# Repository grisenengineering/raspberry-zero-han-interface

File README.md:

# raspberry-zero-han-interface

## Intruduction
This is a simple PCB to allow a raspberry pi zero to connect to smart meters to gather statistics of power comsumption and similar. 
It uses the HAN-interface that many new meters have and converts it to UART signals to the raspberry pi zero.

It adds as a shield for the raspbery pi zero and provides power to the pi from the 5V-line in the HAN-interface. 
The HAN-interface is specified for 250mA max, so even though is could be plugged in to a normal a normal raspberry pi, it is not a good idea...

This board uses a RJ12-connector. Swedish smart meters use this connector and many other countries at least in the EU, but there are variations.

THE BOARD IS NOT TESTED, USE AT YOUR OWN RISK!

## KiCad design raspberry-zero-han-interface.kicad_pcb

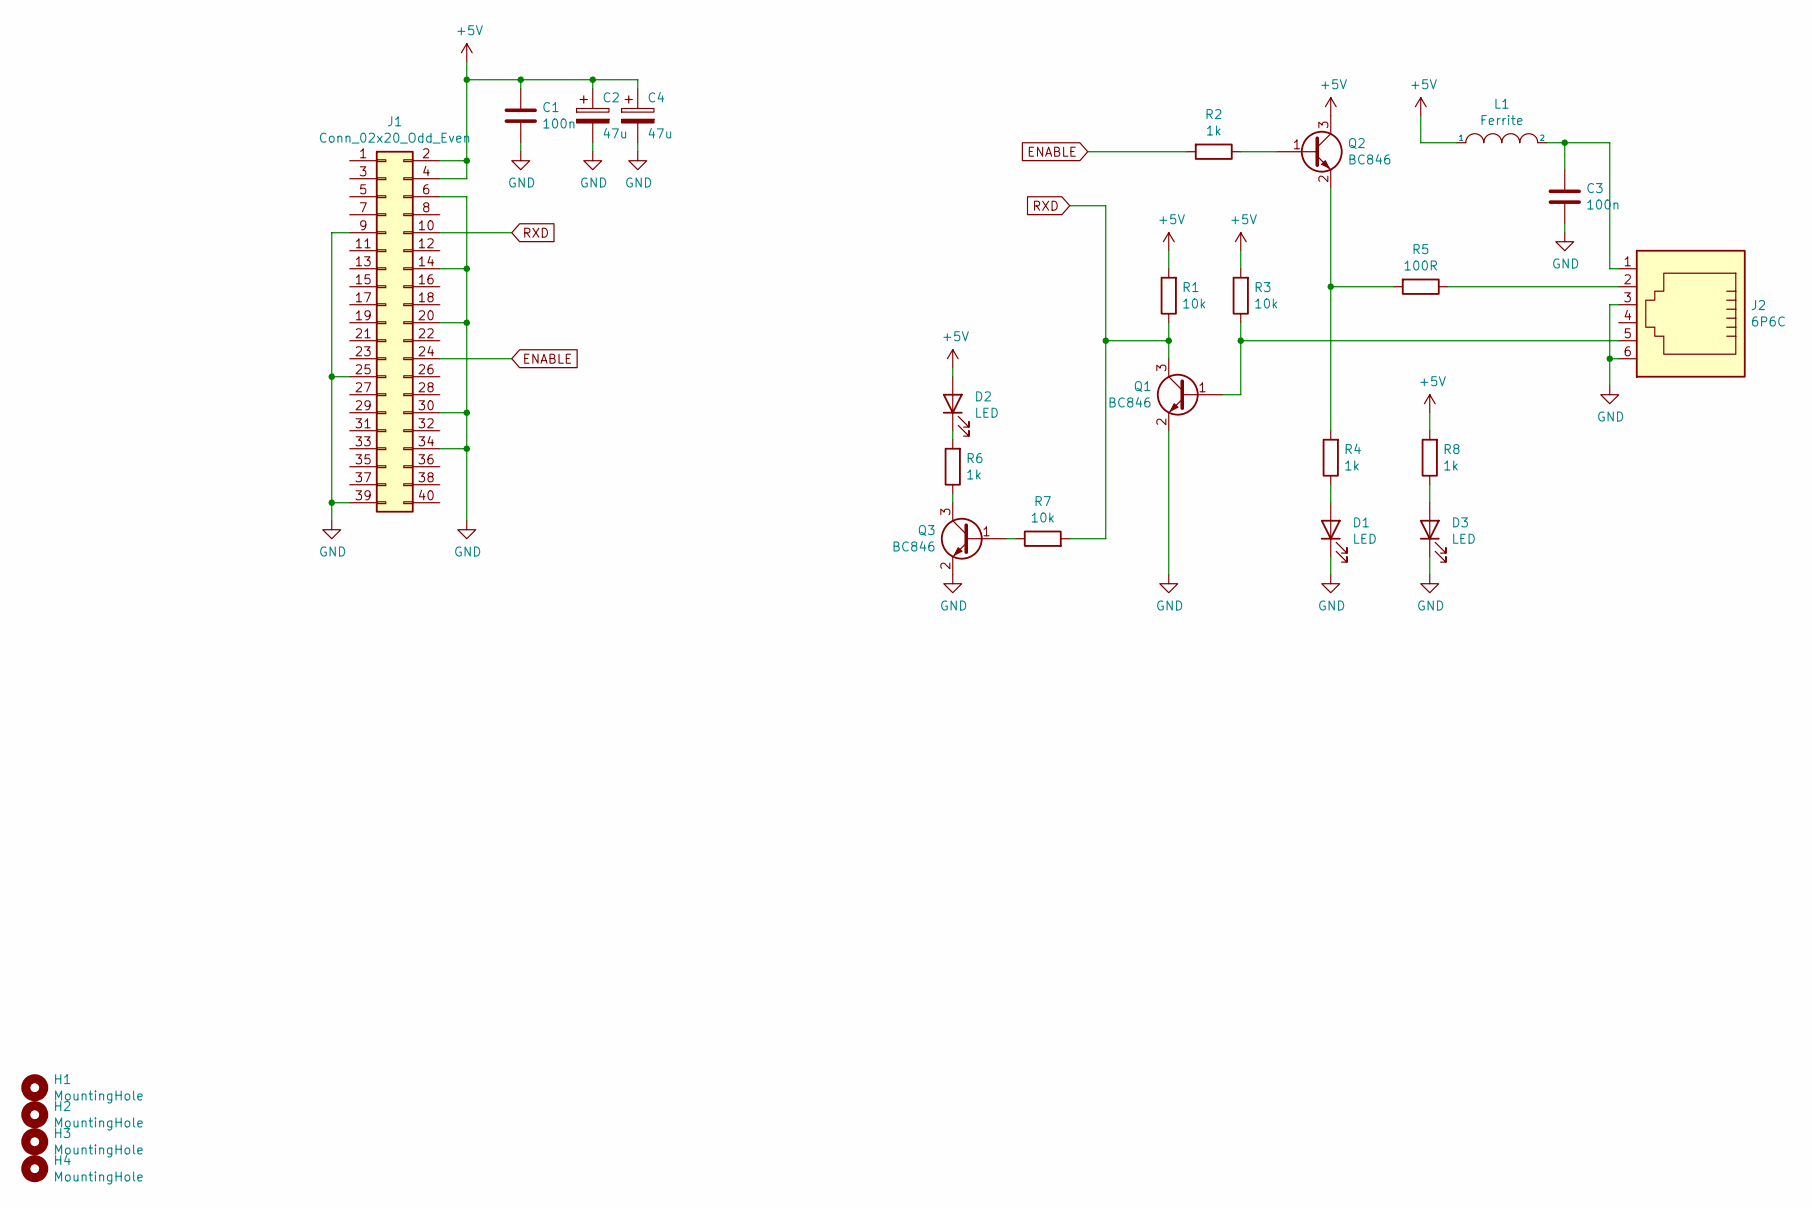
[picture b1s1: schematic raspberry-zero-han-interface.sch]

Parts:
C1, C3: 100n; C_0805_2012Metric
C2: 47u; CP_Elec_6.3x5.4_Nichicon
C4: 47u; CP_Elec_6.3x3
D1, D2, D3: LED; LED_0805_2012Metric
H1, H2, H3, H4: MountingHole; MountingHole_2.5mm
J1: Conn_02x20_Odd_Even; PinHeader_2x20_P2.54mm_Vertical
J2: 6P6C; RJ12_Amphenol_54601
L1: Ferrite; L_0805_2012Metric
Q1, Q2, Q3: BC846; SOT-23
R1, R3, R7: 10k; R_0805_2012Metric
R2, R4, R6, R8: 1k; R_0805_2012Metric
R5: 100R; R_0805_2012Metric

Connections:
+5V: C1.1, C2.1, C4.1, D2.2 (A), J1.2, J1.4, L1.1, Q2.3 (C), R1.2, R3.2, R8.2
ENABLE: J1.24, R2.2
GND: C1.2, C2.2, C3.2, C4.2, D1.1 (K), D3.1 (K), J1.6, J1.9, J1.14, J1.20, J1.25, J1.30, J1.34, J1.39, J2.3, J2.6, Q1.2 (E), Q3.2 (E)
unnamed: C3.1, J2.1, L1.2
unnamed: D1.2 (A), R4.1
unnamed: D2.1 (K), R6.2
unnamed: D3.2 (A), R8.1
unnamed: J2.2, R5.1
unnamed: J2.5, Q1.1 (B), R3.1
unnamed: Q2.1 (B), R2.1
unnamed: Q2.2 (E), R4.2, R5.2
unnamed: Q3.1 (B), R7.1
unnamed: Q3.3 (C), R6.1
RXD: J1.10, Q1.3 (C), R1.1, R7.2

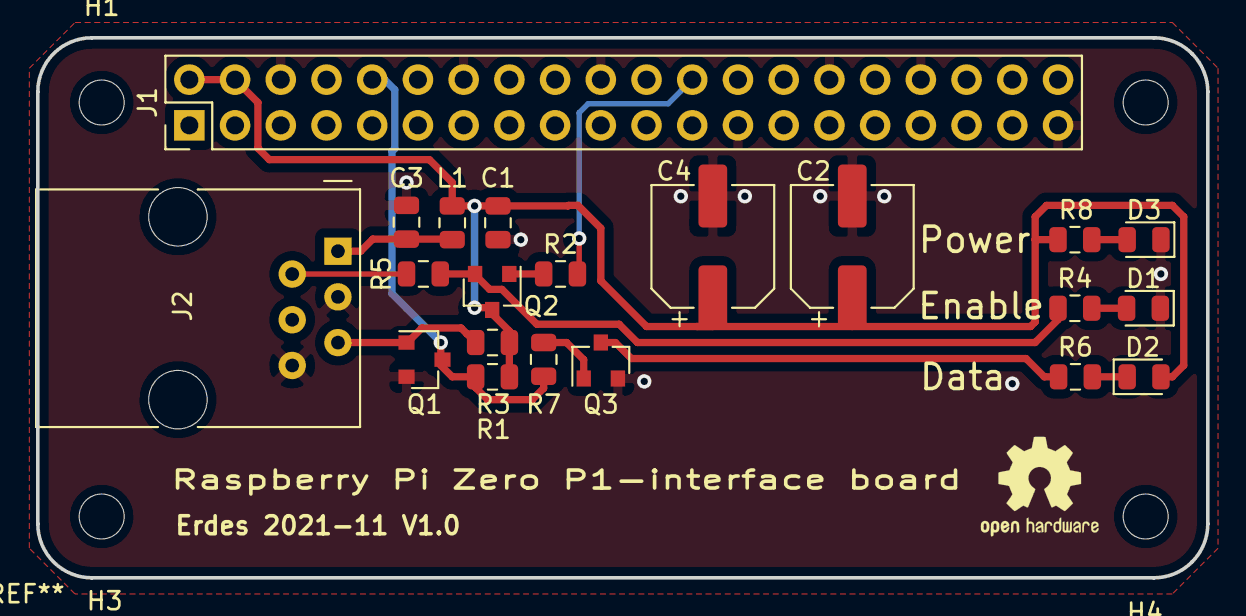
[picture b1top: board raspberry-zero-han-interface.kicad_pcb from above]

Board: 2 copper layers, 65.0 x 30.0 mm, 25 parts (0 on the bottom side), 14 nets.

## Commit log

2022-10-19 Added KiCad .gitignore
2022-10-19 Added KiCad-files to git
